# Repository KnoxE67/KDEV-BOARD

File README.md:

# KDEV-BOARD
My custom rp2040 devboard

## 1/12/2026 - I followed the custom devboard guide  

_Time spent: 3.0h_  

I followed the custom devboard guide until this point: 

"And then, we're going to change the flash memory to what the Pi Pico uses and has a slightly smaller package, which is the W25Q16JVZPIQ TR and uses the PackageSON:WinbondUSON-8-1EP3x2mmP0.5mm_EP0.2x1.6mm footprint, which isn't the exact footprint, but should work fine:" 

which made be confused because there isnt a W25Q16JVZPIQ TR when I looked it up in the footprints:

this is what I have so far: 

## 1/13/2026 6 PM - I followed the guide until I got stuck  

_Time spent: 1.5h_  

I got stuck at this point: Then, hold the route tracks button, and go over to the symbol with 2 traces on it, or just tap 6. Then, go over to your USB-C, and tap on one of the D+/D- pins to start the trace, and route it down to your resistors. If the traces won't go into your resistors pads, that means that your resistors aren't evenly positioned, you can just the relative positioning tool to do this.

And then you can just route the resistors nets into the RP2040 nets (Make sure they're centered so the traces are the same length, you could technically do this as a differential pair if you change your schematic slightly, but it's fine if you just position properly):

this is my problem:

zoomed in:

## 1/13/2026 10 PM - I routed some of the pcb  

_Time spent: 2.0h_  

I started doing the routing of the pcb, this is getting annoying because you have to think of all the connections and trying to make it so that everything can go to where it should go.

Here's a photo of where I am at currently:

## 1/17/2026 - Super close to finishing routing  

_Time spent: 3.0h_  

Almost done routing my pcb but getting very stuck because of the lines and this will probably be the last time doing this project, so sorry but this guide did not make as much sense as the hackpad one did. 

Heres a photo of where Im currently at:

## 1/18/2026 - Well I guess I just need some time to figure it out.  

_Time spent: 1.5h_  

I completely finished all the lines and vias, Everything went well with no errors when drcing and I now think I could do the flight controller, 

here is a photo of my completed devboard:

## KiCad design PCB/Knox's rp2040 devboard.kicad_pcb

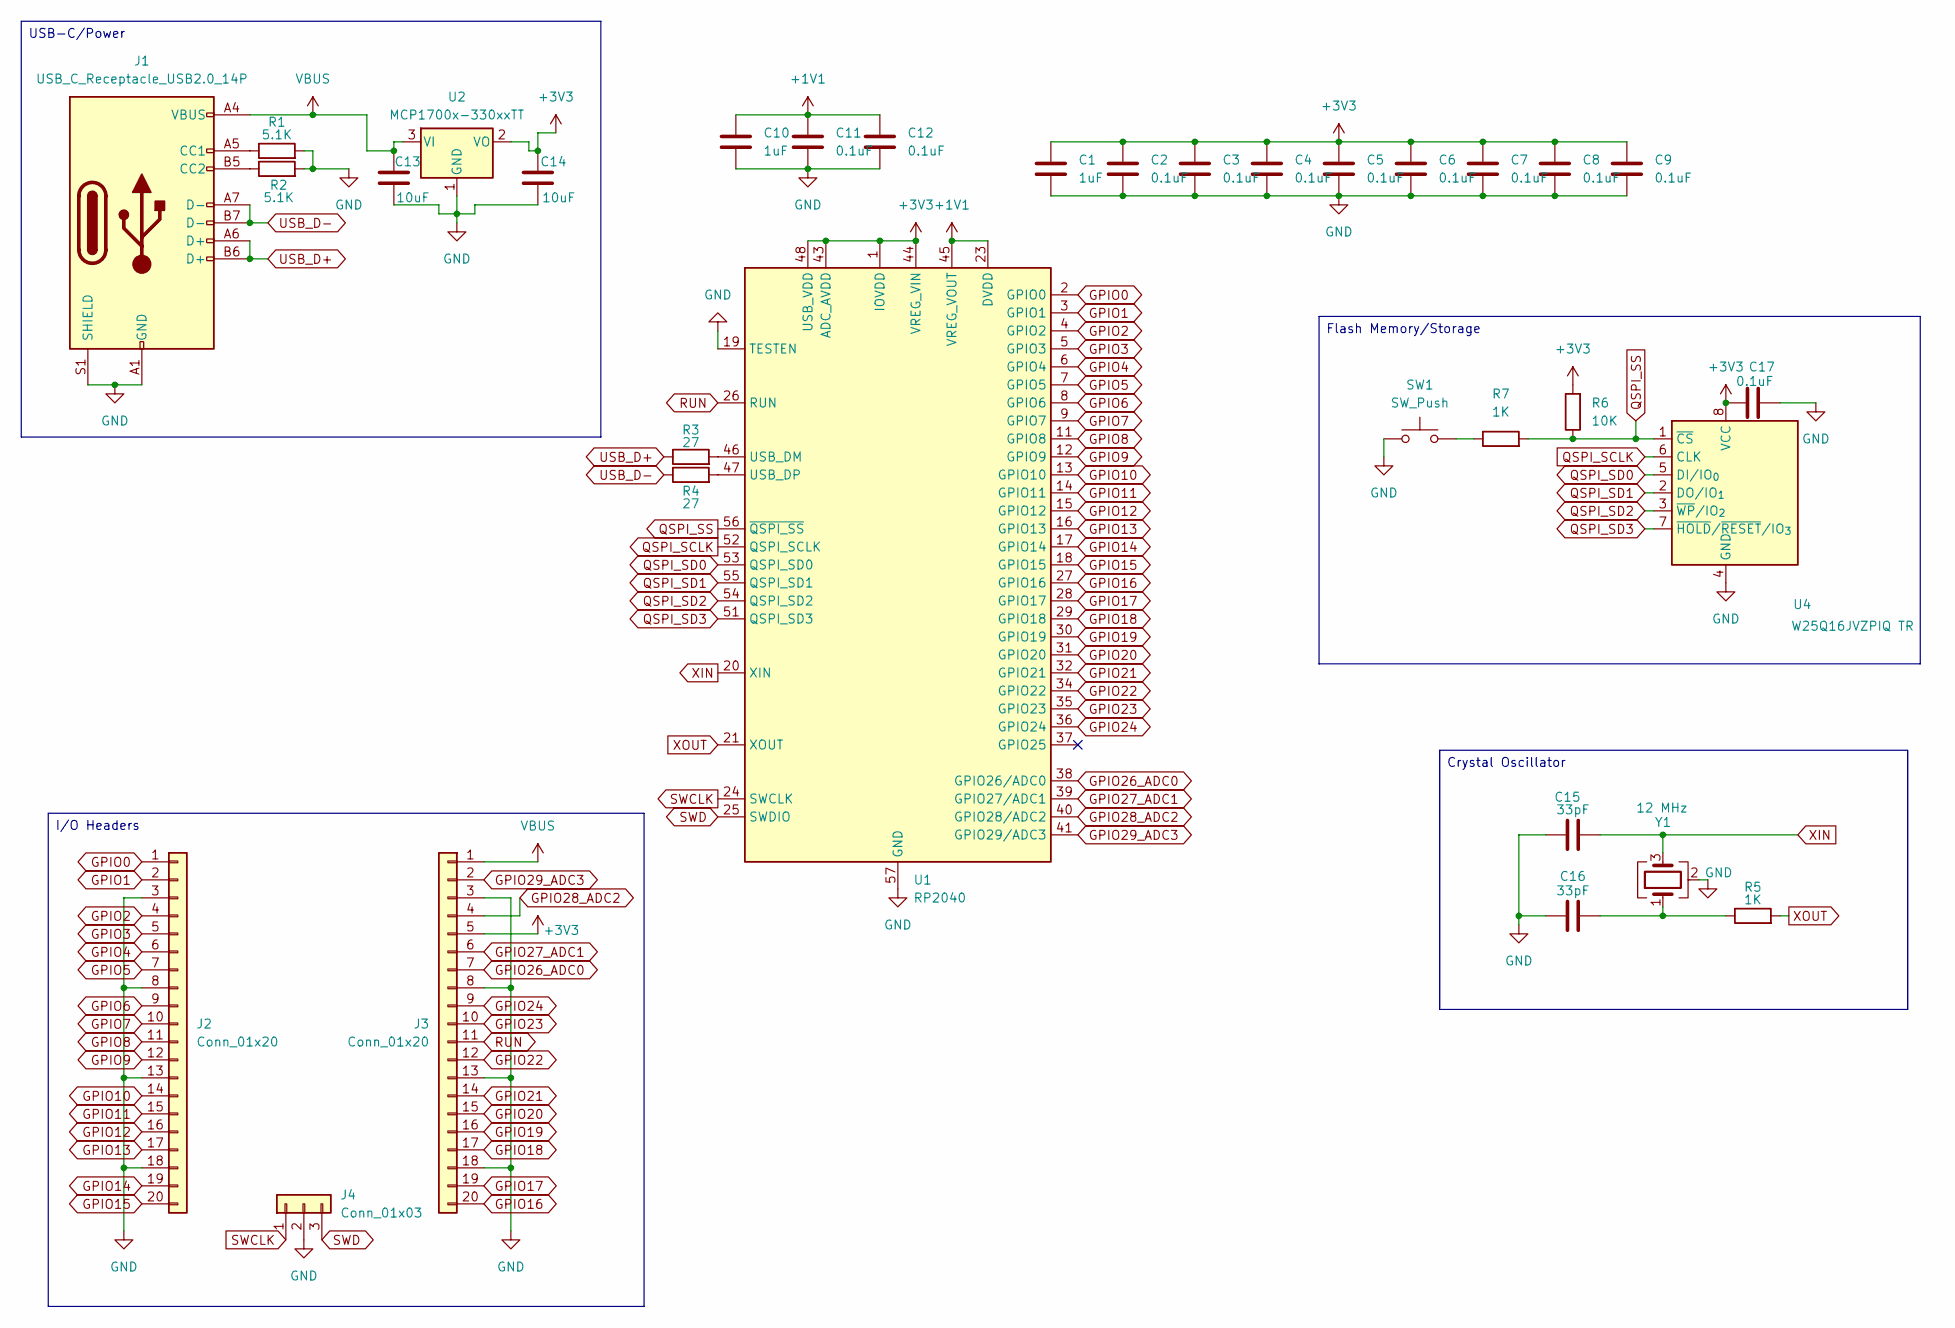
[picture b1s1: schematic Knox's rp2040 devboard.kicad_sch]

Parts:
C1, C10: 1uF; C_0402_1005Metric
C2, C3, C4, C5, C6, C7, C8, C9, C11, C12, C17: 0.1uF; C_0402_1005Metric
C13, C14: 10uF; C_0603_1608Metric
C15, C16: 33pF; C_0402_1005Metric
J1: USB_C_Receptacle_USB2.0_14P; USB_C_Receptacle_HRO_TYPE-C-31-M-12
J2, J3: Conn_01x20; PinHeader_1x20_P2.54mm_Vertical
J4: Conn_01x03; PinHeader_1x03_P2.54mm_Vertical
R1, R2: 5.1K; R_0402_1005Metric
R3, R4: 27; R_0402_1005Metric
R5, R7: 1K; R_0402_1005Metric
R6: 10K; R_0402_1005Metric
SW1: SW_Push; SW_Push_SPST_NO_Alps_SKRK
U1: RP2040; QFN-56-1EP_7x7mm_P0.4mm_EP3.2x3.2mm
U2: MCP1700x-330xxTT; SOT-23
U4: W25Q16JVZPIQ TR; Winbond_USON-8-1EP_3x2mm_P0.5mm_EP0.2x1.6mm
Y1: 12 MHz; Crystal_SMD_3225-4Pin_3.2x2.5mm

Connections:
+1V1: C10.1, C11.1, C12.1, U1.23 (DVDD), U1.45 (VREG_VOUT), U1.50 (DVDD)
+3V3: C1.1, C2.1, C3.1, C4.1, C5.1, C6.1, C7.1, C8.1, C9.1, C14.1, C17.1, J3.5, R6.2, U1.1 (IOVDD), U1.10 (IOVDD), U1.22 (IOVDD), U1.33 (IOVDD), U1.42 (IOVDD), U1.43 (ADC_AVDD), U1.44 (VREG_VIN), U1.48 (USB_VDD), U1.49 (IOVDD), U2.2 (VO), U4.8 (VCC)
GND: C1.2, C2.2, C3.2, C4.2, C5.2, C6.2, C7.2, C8.2, C9.2, C10.2, C11.2, C12.2, C13.2, C14.2, C15.1, C16.1, C17.2, J1.A1 (GND), J1.A12 (GND), J1.B1 (GND), J1.B12 (GND), J1.S1 (SHIELD), J2.3, J2.8, J2.13, J2.18, J3.3, J3.8, J3.13, J3.18, J4.2, R1.2, R2.2, SW1.1, U1.19 (TESTEN), U1.57 (GND), U2.1 (GND), U4.4 (GND), Y1.2 (G), Y1.4 (G)
GPIO0: J2.1, U1.2 (GPIO0)
GPIO1: J2.2, U1.3 (GPIO1)
GPIO2: J2.4, U1.4 (GPIO2)
GPIO3: J2.5, U1.5 (GPIO3)
GPIO4: J2.6, U1.6 (GPIO4)
GPIO5: J2.7, U1.7 (GPIO5)
GPIO6: J2.9, U1.8 (GPIO6)
GPIO7: J2.10, U1.9 (GPIO7)
GPIO8: J2.11, U1.11 (GPIO8)
GPIO9: J2.12, U1.12 (GPIO9)
GPIO10: J2.14, U1.13 (GPIO10)
GPIO11: J2.15, U1.14 (GPIO11)
GPIO12: J2.16, U1.15 (GPIO12)
GPIO13: J2.17, U1.16 (GPIO13)
GPIO14: J2.19, U1.17 (GPIO14)
GPIO15: J2.20, U1.18 (GPIO15)
GPIO16: J3.20, U1.27 (GPIO16)
GPIO17: J3.19, U1.28 (GPIO17)
GPIO18: J3.17, U1.29 (GPIO18)
GPIO19: J3.16, U1.30 (GPIO19)
GPIO20: J3.15, U1.31 (GPIO20)
GPIO21: J3.14, U1.32 (GPIO21)
GPIO22: J3.12, U1.34 (GPIO22)
GPIO23: J3.10, U1.35 (GPIO23)
GPIO24: J3.9, U1.36 (GPIO24)
GPIO26_ADC0: J3.7, U1.38 (GPIO26/ADC0)
GPIO27_ADC1: J3.6, U1.39 (GPIO27/ADC1)
GPIO28_ADC2: J3.4, U1.40 (GPIO28/ADC2)
GPIO29_ADC3: J3.2, U1.41 (GPIO29/ADC3)
unnamed: C16.2, R5.1, Y1.1
unnamed: J1.A5 (CC1), R1.1
unnamed: J1.B5 (CC2), R2.1
unnamed: R7.1, SW1.2
unnamed: R3.2, U1.46 (USB_DM)
unnamed: R4.2, U1.47 (USB_DP)
QSPI_SCLK: U1.52 (QSPI_SCLK), U4.6 (CLK)
QSPI_SD0: U1.53 (QSPI_SD0), U4.5 (DI/IO_{0})
QSPI_SD1: U1.55 (QSPI_SD1), U4.2 (DO/IO_{1})
QSPI_SD2: U1.54 (QSPI_SD2), U4.3 (~WP/IO_{2})
QSPI_SD3: U1.51 (QSPI_SD3), U4.7 (~HOLD/~RESET/IO_{3})
QSPI_SS: R6.1, R7.2, U1.56 (~QSPI_SS), U4.1 (~CS)
RUN: J3.11, U1.26 (RUN)
SWCLK: J4.1, U1.24 (SWCLK)
SWD: J4.3, U1.25 (SWDIO)
USB_D+: J1.A6 (D+), J1.B6 (D+), R3.1
USB_D-: J1.A7 (D-), J1.B7 (D-), R4.1
VBUS: C13.1, J1.A4 (VBUS), J1.A9 (VBUS), J1.B4 (VBUS), J1.B9 (VBUS), J3.1, U2.3 (VI)
XIN: C15.2, U1.20 (XIN), Y1.3
XOUT: R5.2, U1.21 (XOUT)

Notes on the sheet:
I/O Headers
Crystal Oscillator
USB-C/Power
Flash Memory/Storage

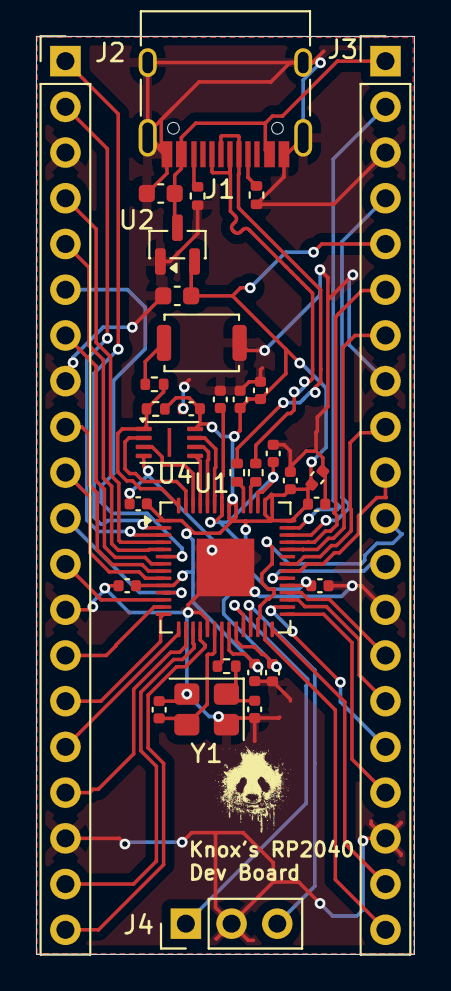
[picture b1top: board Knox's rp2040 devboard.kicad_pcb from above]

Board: 2 copper layers, 21.0 x 51.0 mm, 33 parts (0 on the bottom side), 52 nets.

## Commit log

2026-01-18 added pcb folder
2026-01-18 changed pcb file
2026-01-18 added image to pcb
2026-01-19 added pcb jlcpcb stuff
